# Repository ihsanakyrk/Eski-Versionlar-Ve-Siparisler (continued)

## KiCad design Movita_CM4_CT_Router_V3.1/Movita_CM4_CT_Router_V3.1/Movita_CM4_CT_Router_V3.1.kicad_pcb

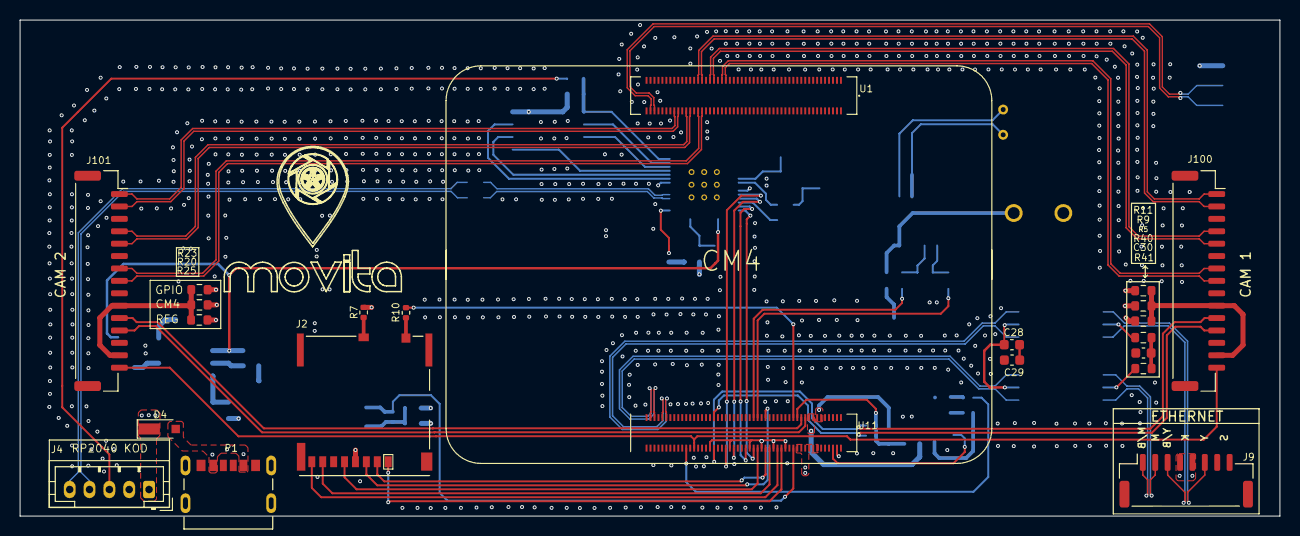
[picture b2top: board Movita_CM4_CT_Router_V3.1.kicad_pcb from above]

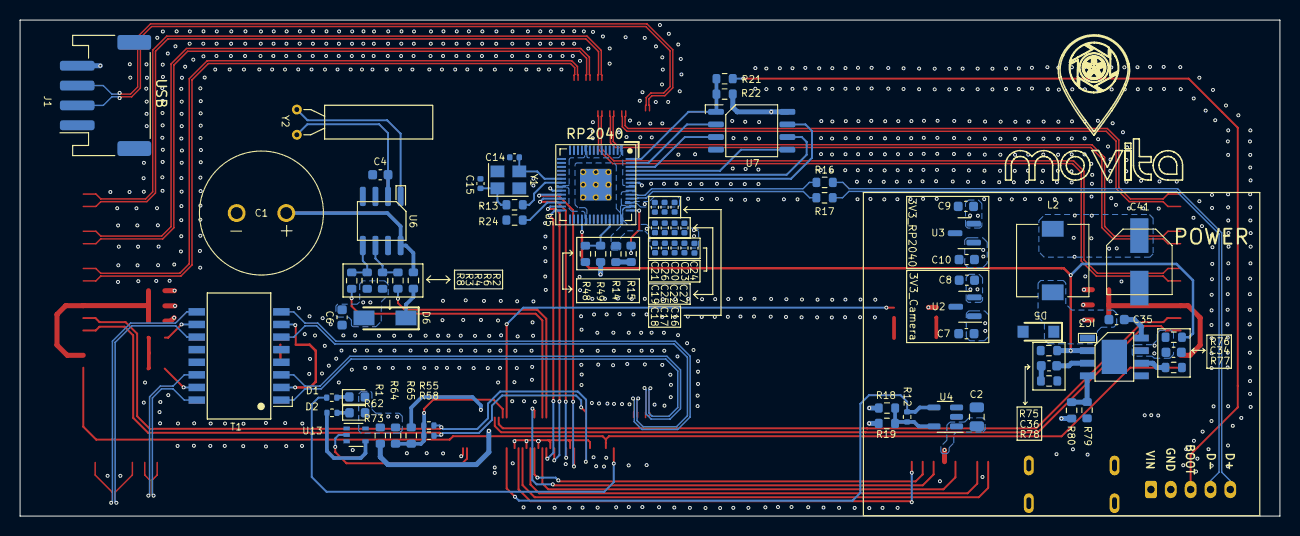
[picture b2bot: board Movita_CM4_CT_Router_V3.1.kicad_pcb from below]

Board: 6 copper layers, 127.0 x 50.0 mm, 96 parts (74 on the bottom side), 100 nets.

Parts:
C1: SE-5R5 D224VYV (C-Type); SuperCapacitor
C2: 10u; C_0805_2012Metric
C4: 22pF; C_0603_1608Metric
C6, C35: 100nF; C_0603_1608Metric
C7, C8, C9, C10, C34: 10uF; C_0603_1608Metric
C14, C15: 27pF; C_0402_1005Metric
C16, C17, C20, C21, C22, C23, C24, C25, C26, C27: 100nF; C_0402_1005Metric
C18, C19: 1uF; C_0402_1005Metric
C28, C29: 0.01uF; C_0603_1608Metric
C30: 1000pF; C_0603_1608Metric
C36: 150pF; C_0603_1608Metric
C41: 100uF; CAPAE660X550N
D1: LED Green; LED_0603_1608Metric
D2: LED Red; LED_0603_1608Metric
D4: 2SS100L-W; 2SS100LW
D5: SS34FA
D6: SS14
IC3: MP1584EN; MP1584N
J1: JST_PH_S4B-PH-SM4-TB_1x04-1MP_P2.00mm_Horizontal_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; JST_PH_S4B-PH-SM4-TB_1x04-1MP_P2.00mm_Horizontal
J2: Micro_SD_Card_Det; SDCARD_MOLEX_503398-1892
J4: JST_PH_B5B-PH-K_1x05_P2.00mm_Vertical
J9: JST_1x8-1MP_P1.25mm_Vertical; JST_1x8_1MP_P1.25mm_Vertical
J100, J101: JST_1x15-1MP_P1.25mm_Vertical; JST_1x15-1MP_P1.25mm_Horizontal
L2: CDRH74NP-100MC-B; CDRH74NP100MCB
P1: TYPE-C 6P(073)
R1, R6, R8, R11, R18, R20, R24, R64: 0R; R_0603_1608Metric
R2: 150R; R_0603_1608Metric
R3, R4: 4.7K; R_0603_1608Metric
R5, R9, R19, R22, R23, R25, R65: DNP; R_0603_1608Metric
R7, R10: DNP; R_0402_1005Metric
R12: 12K 1%; R_0402_1005Metric
R13, R21, R48: 1K; R_0603_1608Metric
R14: 200R; R_0603_1608Metric
R15: 1R; R_0603_1608Metric
R16, R17: 27R; R_0603_1608Metric
R40, R41: 75R; R_0603_1608Metric
R49: 10K; R_0603_1608Metric
R55, R58: 2.2K 1%; R_0402_1005Metric
R62, R73: 1K; R_0402_1005Metric
R75: 2.2K; R_0603_1608Metric
R76, R78: 100K; R_0603_1608Metric
R77: 200K; R_0603_1608Metric
R79: 40.2K; R_0603_1608Metric
R80: 210K; R_0603_1608Metric
T1: H1102NL
U1: DF40C-100DS-0.4V; DF40C-100DS-0.4V_CM4_Unit_B
U2, U3: TLV76033DBZT; SOT-23
U4: RT9742GGJ5; SOT-23-5
U5: RP2040; RP2040-QFN-56
U6: PCF8563T; SOIC-8_3.9x4.9mm_P1.27mm
U7: W25Q128JVS; SOIC-8_5.23x5.23mm_P1.27mm
U11: DF40C-100DS-0.4V; DF40C-100DS-0.4V_CM4_Unit_A
U13: 74LVC1G07SE-7; SOT-353_SC-70-5
Y1: CRYSTAL 12MHz; Crystal_SMD_3225-4Pin_3.2x2.5mm
Y2: CRYSTAL 32.7680KHZ 12.5PF TH; Crystal_AT310_D3.0mm_L10.0mm_Horizontal

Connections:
+1V1: C16.1, C17.1, C18.1, U5.23 (DVDD), U5.45 (VREG_VOUT), U5.50 (DVDD)
/CM4/3.3V_Sensor: C6.1, C7.2, D6.2, R3.1, R4.1, R5.1, R19.1, R25.1, U2.1 (OUT)
/CM4/+1.8v: R65.1, U11.88 (+1.8v_(Output)), U11.90 (+1.8v_(Output))
/CM4/+5V: C41.1, J1.4, L2.2, R80.2, U11.77 (+5v_(Input)), U11.79 (+5v_(Input)), U11.81 (+5v_(Input)), U11.83 (+5v_(Input)), U11.85 (+5v_(Input)), U11.87 (+5v_(Input))
/CM4/CAM0_C_N: J100.7, U1.140 (CAM0_C_N)
/CM4/CAM0_C_P: J100.8, U1.142 (CAM0_C_P)
/CM4/CAM0_D0_N: J100.1, U1.128 (CAM0_D0_N)
/CM4/CAM0_D0_P: J100.2, U1.130 (CAM0_D0_P)
/CM4/CAM0_D1_N: J100.4, U1.134 (CAM0_D1_N)
/CM4/CAM0_D1_P: J100.5, U1.136 (CAM0_D1_P)
/CM4/CAM1_C_N: J101.7, U1.127 (CAM1_C_N)
/CM4/CAM1_C_P: J101.8, U1.129 (CAM1_C_P)
/CM4/CAM1_D0_N: J101.1, U1.115 (CAM1_D0_N)
/CM4/CAM1_D0_P: J101.2, U1.117 (CAM1_D0_P)
/CM4/CAM1_D1_N: J101.4, U1.121 (CAM1_D1_N)
/CM4/CAM1_D1_P: J101.5, U1.123 (CAM1_D1_P)
/CM4/CAM_GPIO: R9.1, R23.1, U11.97 (Camera_GPIO)
/CM4/CM4_+3.3v: D1.2 (A), D2.2 (A), R1.1, R7.1, R11.1, R18.1, R20.1, R64.1, U13.5 (VCC)
/CM4/CM4_PCF_SCL: R4.2, R6.1, U6.6 (SCL)
/CM4/CM4_PCF_SDA: R3.2, R8.1, U6.5 (SDA)
/CM4/GPIO2: R8.2, U11.58 (GPIO2)
/CM4/GPIO3: R6.2, U11.56 (GPIO3)
/CM4/GPIO14: U5.28 (GPIO17), U11.55 (GPIO14)
/CM4/GPIO15: U5.27 (GPIO16), U11.51 (GPIO15)
/CM4/GPIO21: J100.15, J101.15, U11.25 (GPIO21)
/CM4/GPIO24: U5.25 (SWD), U11.45 (GPIO24)
/CM4/GPIO25: U5.24 (SWCLK), U11.41 (GPIO25)
/CM4/GPIO_VREF: R55.1, R58.1, R64.2, R65.2, U11.78 (GPIO_VREF(1.8v/3.3v_Input))
/CM4/ID_SC: J100.11, R55.2, U11.35 (ID_SC)
/CM4/ID_SD: J100.12, R58.2, U11.36 (ID_SD)
/CM4/Reserved: R10.1, U11.76 (Reserved)
/CM4/SCL0: J101.11, U11.80 (SCL0)
/CM4/SDA0: J101.12, U11.82 (SDA0)
/CM4/SD_CLK: J2.5 (CLK), U11.57 (SD_CLK)
/CM4/SD_CMD: J2.3 (CMD), U11.62 (SD_CMD)
/CM4/SD_DAT0: J2.7 (DAT0), U11.63 (SD_DAT0)
/CM4/SD_DAT1: J2.8 (DAT1), U11.67 (SD_DAT1)
/CM4/SD_DAT2: J2.1 (DAT2), U11.69 (SD_DAT2)
/CM4/SD_DAT3: J2.2 (DAT3/CD), U11.61 (SD_DAT3)
/CM4/SD_PWR: C2.1, J2.4 (VDD), U4.1 (OUT)
/CM4/SD_PWR_ON: R12.2, U4.4 (EN), U11.75 (SD_PWR_ON)
/CM4/USB2_N: J1.3, U1.103 (USB2_N)
/CM4/USB2_P: J1.2, U1.105 (USB2_P)
/CM4/nPWR_LED: U11.95 (nPI_LED_PWR), U13.2
/Power Unit/+3V3: C10.2, C19.1, C20.1, C21.1, C22.1, C23.1, C24.1, C25.1, C26.1, C27.1, R14.1, R22.1, U3.1 (OUT), U5.1 (IOVDD), U5.10 (IOVDD), U5.22 (IOVDD), U5.33 (IOVDD), U5.42 (IOVDD), U5.44 (VREG_IN), U5.48 (USB_VDD), U5.49 (IOVDD), U7.8 (VCC)
/Power Unit/VIN: C8.2, C9.2, C34.2, D4.1, IC3.7 (VIN), J4.1, R49.1, R76.1, U2.2 (IN), U3.2 (IN)
/RP2040/GPIO21: IC3.2 (EN), R75.1, R76.2, U5.32 (GPIO21)
/RP2040/GPIO27_ADC1: R48.1, R49.2, U5.39 (GPIO27_ADC1)
/RP2040/QSPI_SCLK: U5.52 (QSPI_SCLK), U7.6 (CLK)
/RP2040/QSPI_SD0: U5.53 (QSPI_SD0), U7.5 (DI(IO0))
/RP2040/QSPI_SD1: U5.55 (QSPI_SD1), U7.2 (DO(IO1))
/RP2040/QSPI_SD2: U5.54 (QSPI_SD2), U7.3 (IO2)
/RP2040/QSPI_SD3: U5.51 (QSPI_SD3), U7.7 (IO3)
/RP2040/QSPI_SS: R21.1, R22.2, U5.56 (QSPI_SS), U7.1 (~CS)
/RP2040/USB_D+: R16.2, U5.47 (USB_DP)
/RP2040/USB_D-: R17.2, U5.46 (USB_DM)
/RP2040/USB_RP2040_D+: J4.5, R16.1
/RP2040/USB_RP2040_D-: J4.4, R17.1
/RP2040/XIN: C14.1, U5.20 (XIN), Y1.3
/RP2040/XOUT: R13.1, U5.21 (XOUT)
/RP2040/~USB_BOOT: J4.3, R21.2
ADC_VREF: R14.2, R15.1
GND: C1.2, C2.2, C4.2, C6.2, C7.1, C8.1, C9.1, C10.1, C14.2, C15.2, C16.2, C17.2, C18.2, C19.2, C20.2, C21.2, C22.2, C23.2, C24.2, C25.2, C26.2, C27.2, C29.2, C30.2, C34.1, C41.2, D5.2, IC3.5 (GND), IC3.9 (EP), J1.1, J2.6 (VSS), J2.11 (SHIELD), J4.2, J9.7, J9.8, J9.MP, J100.3, J100.6, J100.9, J100.13, J101.3, J101.6, J101.9, J101.13, P1.A12 (GND), P1.B12 (GND), P1.MP (SHIELD), R48.2, R75.2, R77.2, R78.2, R79.2, U1.107 (GND), U1.108 (GND), U1.113 (GND), U1.114 (GND), U1.119 (GND), U1.120 (GND), U1.125 (GND), U1.126 (GND), U1.131 (GND), U1.132 (GND), U1.137 (GND), U1.138 (GND), U1.144 (GND), U1.150 (GND), U1.155 (GND), U1.156 (GND), U1.161 (GND), U1.162 (GND), U1.167 (GND), U1.168 (GND), U1.173 (GND), U1.174 (GND), U1.179 (GND), U1.180 (GND), U1.185 (GND), U1.186 (GND), U1.191 (GND), U1.192 (GND), U1.197 (GND), U1.198 (GND), U2.3 (GND), U3.3 (GND), U4.2 (GND), U5.19 (TESTEN), U5.57 (GND), U6.4 (VSS), U7.4 (GND), U11.1 (GND), U11.2 (GND), U11.7 (GND), U11.8 (GND), U11.13 (GND), U11.14 (GND), U11.22 (GND), U11.23 (GND), U11.32 (GND), U11.33 (GND), U11.42 (GND), U11.43 (GND), U11.52 (GND), U11.53 (GND), U11.59 (GND), U11.60 (GND), U11.65 (GND), U11.66 (GND), U11.71 (GND), U11.74 (GND), U11.98 (GND), U13.3 (GND), Y1.2, Y1.4
unnamed: C15.1, R13.2, Y1.1
unnamed: C28.2, C29.1
unnamed: C30.1, R40.1, R41.1
unnamed: C36.1, R78.1
unnamed: D1.1 (K), R62.1
unnamed: D2.1 (K), R73.1
unnamed: D6.1, R2.1
unnamed: C35.2, IC3.8 (BST)
unnamed: C36.2, IC3.3 (COMP)
unnamed: IC3.4 (FB), R79.1, R80.1
unnamed: IC3.6 (FREQ), R77.1
unnamed: C35.1, D5.1, IC3.1 (SW), L2.1
unnamed: J2.10 (DET_A), R7.2
unnamed: J2.9 (DET_B), R10.2
unnamed: J100.10, J100.14, R5.2, R9.2, R11.2
unnamed: J101.10, J101.14, R20.2, R23.2, R25.2
unnamed: R1.2, U11.84 (+3.3v_(Output)), U11.86 (+3.3v_(Output))
unnamed: R73.2, U13.4
unnamed: C28.1, T1.2 (CT1), T1.7 (CT2)
unnamed: R40.2, T1.10 (CT3)
unnamed: R41.2, T1.15 (CT4)
unnamed: R12.1, R18.2, R19.2, U4.5 (IN)
unnamed: R15.2, U5.43 (ADC_AVDD)
unnamed: R24.1, U5.26 (RUN)
unnamed: U6.1 (OSCI), Y2.2
unnamed: C4.1, U6.2 (OSCO), Y2.1
unnamed: C1.1, R2.2, U6.8 (VDD)
unnamed: R62.2, U11.21 (PI_nLED_Activity)
RX_N: T1.8 (RD-), U11.12 (Ethernet_Pair0_P)
RX_P: T1.6 (RD+), U11.10 (Ethernet_Pair0_N)
TRD0_N: J9.2, T1.14 (TX-)
TRD0_P: J9.1, T1.16 (TX+)
TRD1_N: J9.6, T1.9 (RX-)
TRD1_P: J9.3, T1.11 (RX+)
TX_N: T1.3 (TD-), U11.6 (Ethernet_Pair1_N)
TX_P: T1.1 (TD+), U11.4 (Ethernet_Pair1_P)
VRAW: D4.2, J9.4, J9.5, P1.A9 (VBUS), P1.B9 (VBUS)

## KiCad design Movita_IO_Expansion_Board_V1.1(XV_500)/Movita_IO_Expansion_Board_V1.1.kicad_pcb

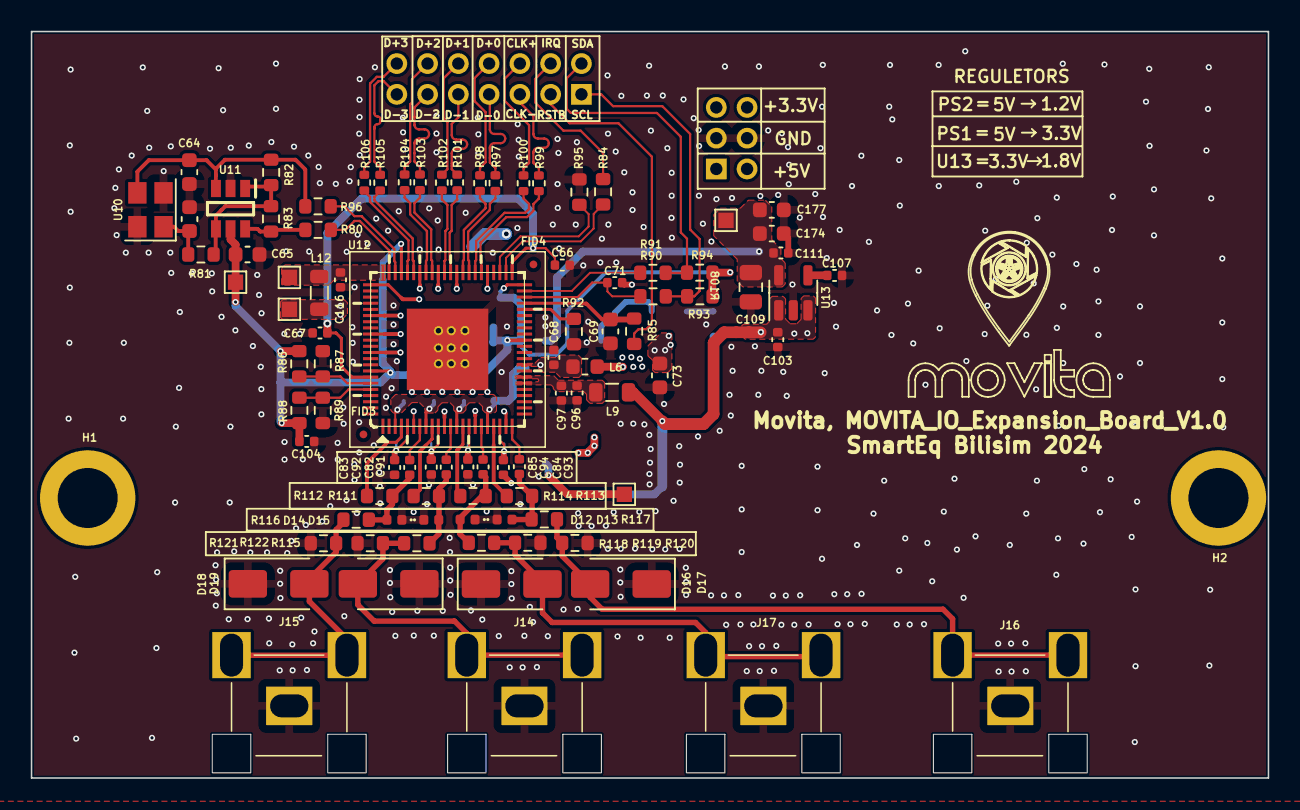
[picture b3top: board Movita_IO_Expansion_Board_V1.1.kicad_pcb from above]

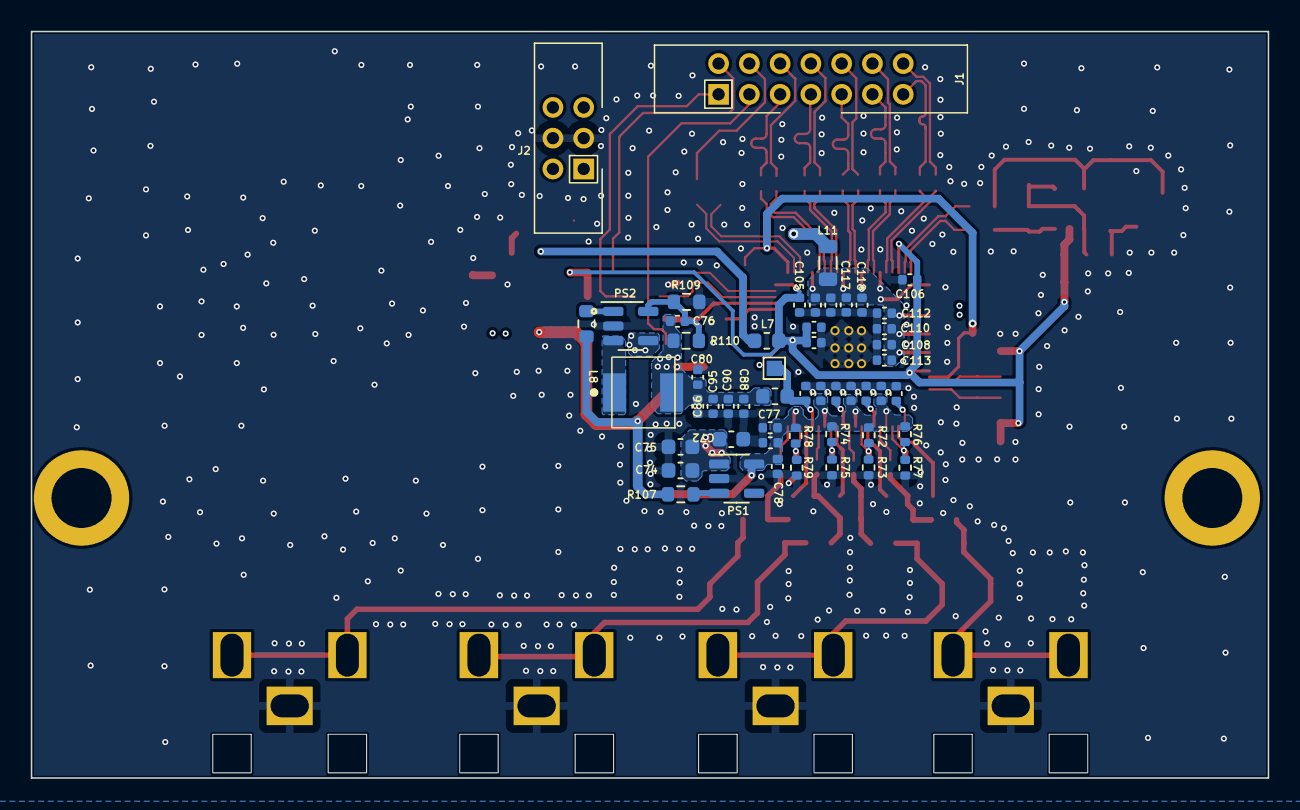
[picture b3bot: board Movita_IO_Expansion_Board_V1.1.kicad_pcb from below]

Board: 4 copper layers, 80.4 x 48.5 mm, 146 parts (52 on the bottom side), 75 nets.

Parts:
C63, C64: 8pF; C_0603_1608Metric
C65: 1uF; C_0603_1608Metric
C66, C67, C68, C70, C79, C81, C82, C83, C84, C85, C87, C89, C90, C91, C92, C93, C94, C95, C96, C98, C99, C100, C101, C102, C103, C104, C105, C106, C107, C108, C110, C111, C112, C113, C114, C115, C116, C117, C118: 100nF; C_0402_1005Metric
C69: 1nF; C_0603_1608Metric
C71: 56pF; C_0402_1005Metric
C72, C73: 10uF; C_0603_1608Metric
C74, C75, C177: 100nF; C_0603_1608Metric
C76: 100pF; C_0402_1005Metric
C77, C80, C86: 10uF; C_0402_1005Metric
C78, C88, C97: 4.7uF; C_0402_1005Metric
C109: 10uF; C_0805_2012Metric
C174: 4.7uF; C_0603_1608Metric
D12, D13, D14, D15: EZJZ800AA; D_0402_1005Metric
D16, D17, D18, D19: SMAJ30CA; D_SMA
FID3, FID4: DNP; Fiducial_0.5mm_Mask1mm
H1, H2: DNP; Screw_Terminal_1x1
J1: Conn_01x14_Pin; Analog signal connector
J2: Conn_01x06_Pin; Analog power connector
J14, J15, J16, J17: DNP; AV_CON
L6, L7: 742792651; L_0603_1608Metric
L8: YSPI0420-1R0M; HCM0420-1R0M
L9, L11, L12: YI201209U101-3R0T; L_0805_2012Metric
L10: CBW160808U101T; L_0603_1608Metric
PS1: RT9013-33GB; SOT-23-5
PS2: ETA3448S2F; SOT-23-5
R72, R74, R76, R78: 1M; R_0402_1005Metric
R73, R75, R77, R79: 510K; R_0402_1005Metric
R80, R81, R90, R91: 100R; R_0603_1608Metric
R82: 560K; R_0603_1608Metric
R83, R87, R89, R96: DNP; R_0603_1608Metric
R84, R85, R95: 0R; R_0603_1608Metric
R86, R88: 4.7K; R_0603_1608Metric
R92, R115, R116, R117, R118: 22R; R_0603_1608Metric
R93, R94: 2K; R_0603_1608Metric
R97, R98, R99, R100, R101, R102, R103, R104, R105, R106: 22R; R_0402_1005Metric
R107, R108: 10K; R_0603_1608Metric
R109, R110: 150K; R_0603_1608Metric
R111, R112, R113, R114: 47R; R_0603_1608Metric
R119, R120, R121, R122: 75R; R_0603_1608Metric
TP13, TP14, TP15, TP16, TP17, TP22: DNP; TestPoint_Pad_1.0x1.0mm
U10: CF4027M00010; Crystal_SMD_3225-4Pin_3.2x2.5mm
U11: NL27WZU04DTT1G
U12: TP2815; EPQFN_88L_10X10
U13: TP5108E23E-18; SOT-23-5

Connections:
/CSI_AHD/+3.3V: C103.1, J2.5, J2.6, L9.1, R107.1, R108.1, U13.1 (IN), U13.3 (EN)
/CSI_AHD/+5V: C72.1, C73.1, C74.1, C75.1, J2.1, J2.2, PS1.1 (VIN), PS2.4 (IN)
/CSI_AHD/CK1_N: R99.2, U12.50 (CKN_1)
/CSI_AHD/CK1_P: R100.2, U12.51 (CKP_1)
/CSI_AHD/D01_N: R97.2, U12.52 (D0N_1)
/CSI_AHD/D01_P: R98.2, U12.53 (D0P_1)
/CSI_AHD/D11_N: R101.2, U12.55 (D1N_1)
/CSI_AHD/D11_P: R102.2, U12.56 (D1P_1)
/CSI_AHD/D21_N: R103.2, U12.58 (D2N_1)
/CSI_AHD/D21_P: R104.2, U12.59 (D2P_1)
/CSI_AHD/D31_N: R105.2, U12.61 (D3N_1)
/CSI_AHD/D31_P: R106.2, U12.62 (D3P_1)
/CSI_AHD/DVDD: C66.2, C67.2, C68.2, L6.2, U12.31 (DVDD1), U12.45 (DVDD3), U12.82 (DVDD2)
/CSI_AHD/LX: L8.1, PS2.3 (LX)
/CSI_AHD/TP2855_CLK+: J1.6, R100.1
/CSI_AHD/TP2855_CLK-: J1.5, R99.1
/CSI_AHD/TP2855_D+0: J1.8, R98.1
/CSI_AHD/TP2855_D+1: J1.10, R102.1
/CSI_AHD/TP2855_D+2: J1.12, R104.1
/CSI_AHD/TP2855_D+3: J1.14, R106.1
/CSI_AHD/TP2855_D-0: J1.7, R97.1
/CSI_AHD/TP2855_D-1: J1.9, R101.1
/CSI_AHD/TP2855_D-2: J1.11, R103.1
/CSI_AHD/TP2855_D-3: J1.13, R105.1
/CSI_AHD/TP2855_IIC_ADDR0: R86.1, R87.2, U12.83 (SAD0)
/CSI_AHD/TP2855_IIC_ADDR1: R88.1, R89.2, U12.84 (SAD1)
/CSI_AHD/TP2855_IRQ: J1.4, R84.1
/CSI_AHD/TP2855_OSC_CLK_IN: R80.1, U12.65 (XTI)
/CSI_AHD/TP2855_OSC_CLK_OUT: R96.2, U12.64 (XTO)
/CSI_AHD/TP2855_PTZ1: R112.2, U12.4 (PTZ1)
/CSI_AHD/TP2855_PTZ2: R111.2, U12.9 (PTZ2)
/CSI_AHD/TP2855_PTZ3: R114.2, U12.14 (PTZ3)
/CSI_AHD/TP2855_PTZ4: R113.2, U12.19 (PTZ4)
/CSI_AHD/TP2855_RSTB: J1.3, R85.1
/CSI_AHD/TP2855_SCL: J1.1, R90.1, R93.2
/CSI_AHD/TP2855_SDA: J1.2, R91.1, R94.2
/CSI_AHD/TP2855_TEST_MODE: R95.2, U12.47 (TEST)
/CSI_AHD/TP2855_VIN1N: C83.1, R76.1, R77.2, U12.5 (VIN1N)
/CSI_AHD/TP2855_VIN1P: C92.1, U12.7 (VIN1)
/CSI_AHD/TP2855_VIN2N: C82.1, R72.1, R73.2, U12.10 (VIN2N)
/CSI_AHD/TP2855_VIN2P: C91.1, U12.12 (VIN2)
/CSI_AHD/TP2855_VIN3N: C85.1, R74.1, R75.2, U12.15 (VIN3N)
/CSI_AHD/TP2855_VIN3P: C94.1, U12.17 (VIN3)
/CSI_AHD/TP2855_VIN4N: C84.1, R78.1, R79.2, U12.20 (VIN4N)
/CSI_AHD/TP2855_VIN4P: C93.1, U12.22 (VIN4)
/CSI_AHD/TP2855_XOUT: C64.2, R82.2, R96.1, U10.3 (XOUT), U11.3 (INA2)
Earth: C63.1, C64.1, C65.2, C66.1, C67.1, C68.1, C69.1, C70.2, C71.1, C72.2, C73.2, C74.2, C75.2, C77.2, C78.2, C79.2, C80.2, C81.2, C82.2, C83.2, C84.2, C85.2, C86.2, C87.2, C88.2, C89.2, C90.2, C95.2, C96.2, C97.2, C98.2, C99.2, C100.2, C101.2, C102.2, C103.2, C104.2, C105.2, C106.2, C107.2, C108.2, C109.2, C110.2, C111.2, C112.2, C113.2, C114.2, C115.2, C116.2, C117.2, C118.2, C174.2, C177.2, D12.1 (A1), D13.1 (A1), D14.1 (A1), D15.1 (A1), D16.1 (A1), D17.1 (A1), D18.1 (A1), D19.1 (A1), J2.3, J2.4, J14.3, J15.3, J16.3, J17.3, PS1.2 (GND), PS2.2 (GND), R73.1, R75.1, R77.1, R79.1, R87.1, R89.1, R92.1, R95.1, R109.1, R119.2, R120.2, R121.2, R122.2, U10.2 (GND2), U10.4 (GND1), U11.2 (GND), U12.89 (EPAD), U13.2 (GND)
unnamed: C94.2, D12.2 (A2), R114.1, R118.2
unnamed: C93.2, D13.2 (A2), R113.1, R117.2
unnamed: C92.2, D14.2 (A2), R112.1, R116.2
unnamed: C91.2, D15.2 (A2), R111.1, R115.2
unnamed: D16.2 (A2), J17.1, J17.2, R118.1, R119.1
unnamed: D17.2 (A2), J16.1, J16.2, R117.1, R120.1
unnamed: D18.2 (A2), J15.1, J15.2, R116.1, R121.1
unnamed: D19.2 (A2), J14.1, J14.2, R115.1, R122.1
unnamed: PS1.3 (EN), R107.2
unnamed: PS2.1 (EN), R108.2
unnamed: C76.2, PS2.5 (OUT), R109.2, R110.1
unnamed: C63.2, R81.1, U10.1 (XIN)
unnamed: R81.2, R82.1, R83.2, U11.1 (INA1), U11.4 (OUT*Y2)
unnamed: R80.2, R83.1, U11.6 (OUT*Y1)
unnamed: R92.2, U12.40 (ALINKI)
unnamed: R84.2, U12.46 (IRQ)
unnamed: C69.2, R85.2, U12.41 (RSTB)
unnamed: C71.2, R90.2, U12.42 (SCL)
unnamed: R91.2, U12.43 (SDA)
unnamed: C107.1, U13.4 (BP)
TP2855_AVDD1V2: C98.1, C99.1, C100.1, C101.1, L10.2, TP15.1, U12.3 (AVDD1_1), U12.8 (AVDD1_2), U12.13 (AVDD1_3), U12.18 (AVDD1_4)
TP2855_AVDD3V3: C77.1, C78.1, C79.1, C81.1, C87.1, C89.1, PS1.5 (VOUT), R72.2, R74.2, R76.2, R78.2, TP13.1, U12.6 (AVDD3_1), U12.11 (AVDD3_2), U12.16 (AVDD3_3), U12.21 (AVDD3_4)
TP2855_AVDDPLL_1V2: C116.1, L12.2, TP17.1, U12.66 (VDDPPL)
TP2855_CODEC_V3V3: C96.1, C97.1, L9.2, U12.28 (AADVDD), U12.29 (ADAVDD)
TP2855_DVDD1V2: C108.1, C110.1, C112.1, C113.1, C114.1, C115.1, C117.1, C118.1, L11.2, U12.49 (VDDM2_1), U12.54 (VDDM1_1), U12.57 (VDDM3_1), U12.60 (VDDM4_1), U12.67 (VDDM1_2), U12.72 (VDDM4_2), U12.75 (VDDM2_2), U12.78 (VDDM3_2)
TP2855_VCCIO: C65.1, C70.1, C102.1, C104.1, C105.1, C106.1, L7.2, R86.2, R88.2, R93.1, R94.1, TP16.1, U11.5 (VCC), U12.35 (VDD_IO3), U12.44 (VDD_IO1), U12.63 (VDD_IO2), U12.81 (VDD_IO4)
VDDIO_18: C109.1, C111.1, C174.1, C177.1, L7.1, TP22.1, U13.5 (OUT)
VDD_1V2: C76.1, C80.1, C86.1, C88.1, C90.1, C95.1, L6.1, L8.2, L10.1, L11.1, L12.1, R110.2, TP14.1

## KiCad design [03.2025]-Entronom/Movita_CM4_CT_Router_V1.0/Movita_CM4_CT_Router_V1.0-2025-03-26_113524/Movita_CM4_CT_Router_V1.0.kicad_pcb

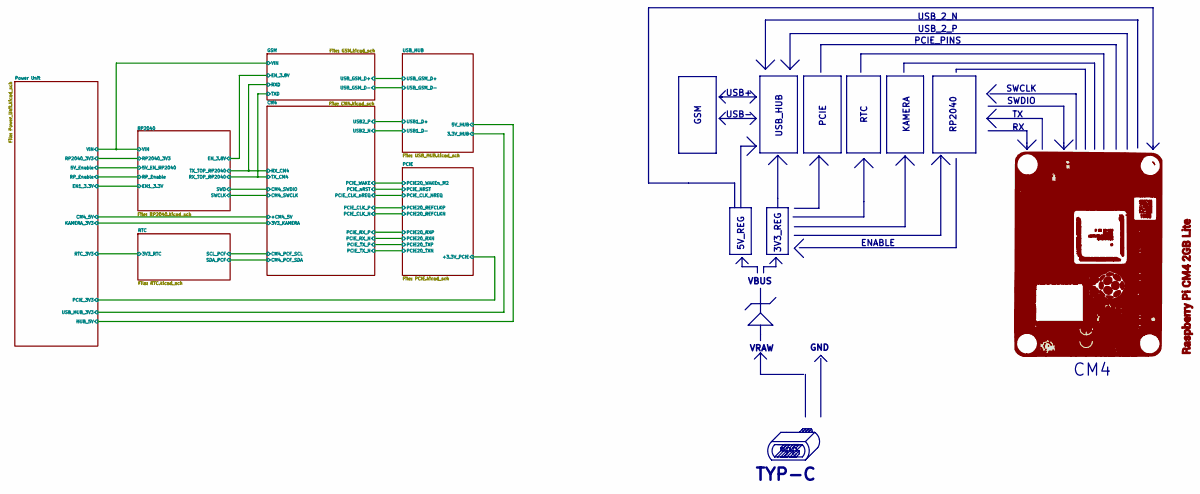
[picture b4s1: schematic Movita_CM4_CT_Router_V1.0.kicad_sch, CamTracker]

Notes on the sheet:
PCIE
PCIE_PINS
GND
5V_REG
SWDIO
KAMERA
CM4
GSM
RTC
USB-
SWCLK
VRAW
VBUS
USB_HUB
USB+
USB_2_N
USB_2_P
TYP-C
ENABLE
3V3_REG
RP2040

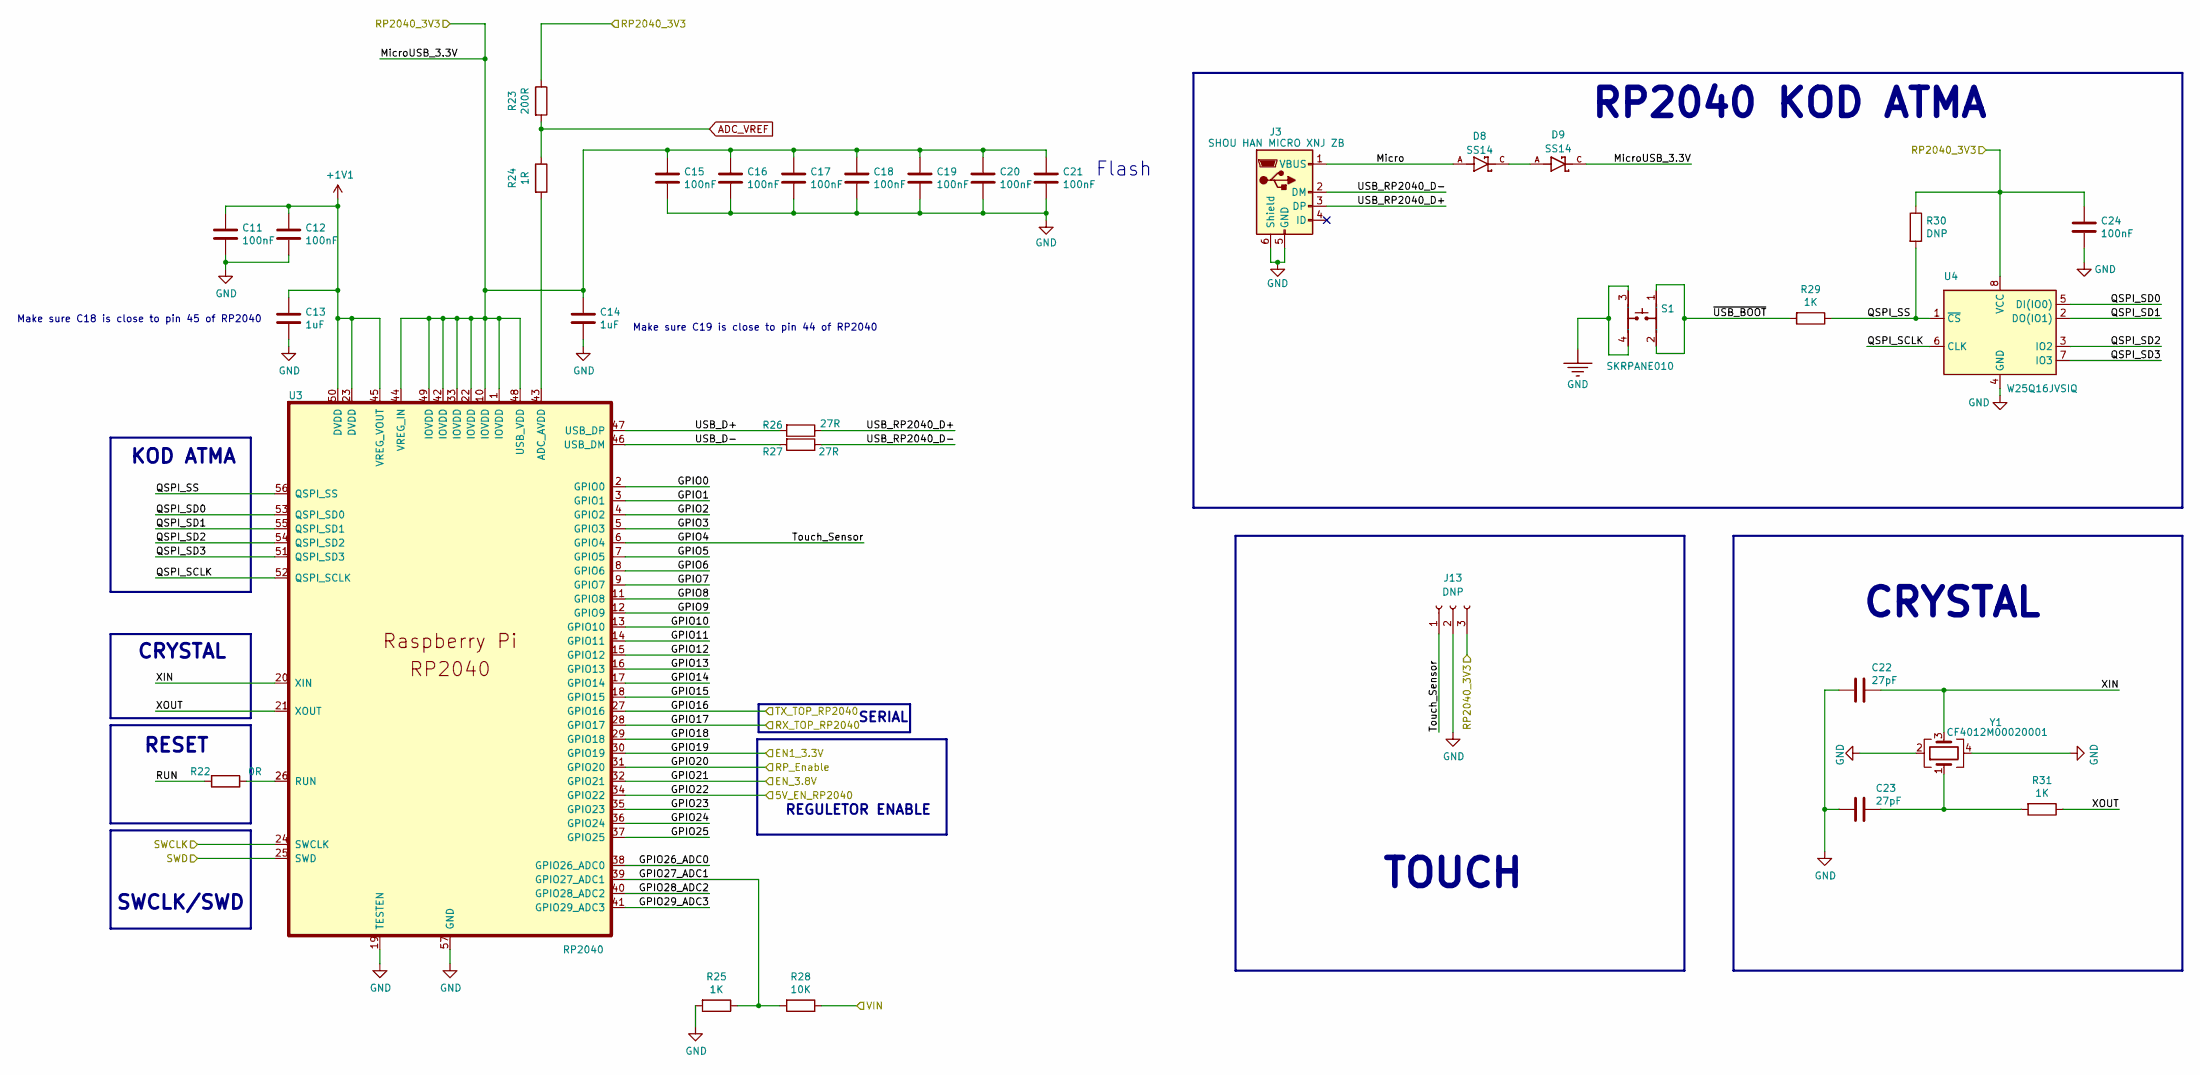
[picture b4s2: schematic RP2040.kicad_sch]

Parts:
C11, C12, C15, C16, C17, C18, C19, C20, C21, C24: 100nF; C_0402_1005Metric
C13, C14: 1uF; C_0402_1005Metric
C22, C23: 27pF; C_0603_1608Metric
D8, D9: SS14
J3: SHOU HAN MICRO XNJ ZB; Micro-B SMD; MPN SHOU HAN MICRO XNJ ZB
J13: DNP; PinSocket_1x03_P2.00mm_Vertical
R22: 0R; R_0402_1005Metric
R23: 200R; R_0402_1005Metric
R24: 1R; R_0402_1005Metric
R25: 1K; R_0402_1005Metric
R26, R27: 27R; R_0603_1608Metric
R28: 10K; R_0402_1005Metric
R29, R31: 1K; R_0603_1608Metric; MPN 0603WAF1001T5E
R30: DNP; R_0603_1608Metric
S1: SKRPANE010
U3: RP2040; RP2040-QFN-56; MPN RP2040
U4: W25Q16JVSIQ; SOIC-8_5.23x5.23mm_P1.27mm; MPN W25Q16JVSIQ
Y1: CF4012M00020001; Crystal_SMD_3225-4Pin_3.2x2.5mm; MPN CF4012M00020001

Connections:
+1V1: C11.1, C12.1, C13.1, U3.23 (DVDD), U3.45 (VREG_VOUT), U3.50 (DVDD)
/CM4/GPIO14: U3.28 (GPIO17); also elsewhere on the board
/CM4/GPIO15: U3.27 (GPIO16); also elsewhere on the board
/CM4/GPIO24: U3.25 (SWD); also elsewhere on the board
/CM4/GPIO25: U3.24 (SWCLK); also elsewhere on the board
/RP2040/GPIO0: U3.2 (GPIO0)
/RP2040/GPIO1: U3.3 (GPIO1)
/RP2040/GPIO2: U3.4 (GPIO2)
/RP2040/GPIO3: U3.5 (GPIO3)
/RP2040/GPIO4: J13.1, U3.6 (GPIO4)
/RP2040/GPIO5: U3.7 (GPIO5)
/RP2040/GPIO6: U3.8 (GPIO6)
/RP2040/GPIO7: U3.9 (GPIO7)
/RP2040/GPIO8: U3.11 (GPIO8)
/RP2040/GPIO9: U3.12 (GPIO9)
/RP2040/GPIO10: U3.13 (GPIO10)
/RP2040/GPIO11: U3.14 (GPIO11)
/RP2040/GPIO12: U3.15 (GPIO12)
/RP2040/GPIO13: U3.16 (GPIO13)
/RP2040/GPIO14: U3.17 (GPIO14)
/RP2040/GPIO15: U3.18 (GPIO15)
/RP2040/GPIO18: U3.29 (GPIO18)
/RP2040/GPIO19: U3.30 (GPIO19); also elsewhere on the board
/RP2040/GPIO20: U3.31 (GPIO20); also elsewhere on the board
/RP2040/GPIO21: U3.32 (GPIO21); also elsewhere on the board
/RP2040/GPIO22: U3.34 (GPIO22); also elsewhere on the board
/RP2040/GPIO23: U3.35 (GPIO23)
/RP2040/GPIO24: U3.36 (GPIO24)
/RP2040/GPIO25: U3.37 (GPIO25)
/RP2040/GPIO26_ADC0: U3.38 (GPIO26_ADC0)
/RP2040/GPIO27_ADC1: R25.1, R28.2, U3.39 (GPIO27_ADC1)
/RP2040/GPIO28_ADC2: U3.40 (GPIO28_ADC2)
/RP2040/GPIO29_ADC3: U3.41 (GPIO29_ADC3)
/RP2040/Micro: D8.A, J3.1 (VBUS)
/RP2040/MicroUSB_3.3V: C14.1, C15.1, C16.1, C17.1, C18.1, C19.1, C20.1, C21.1, C24.1, D9.C, J13.3, R23.1, R30.1, U3.1 (IOVDD), U3.10 (IOVDD), U3.22 (IOVDD), U3.33 (IOVDD), U3.42 (IOVDD), U3.44 (VREG_IN), U3.48 (USB_VDD), U3.49 (IOVDD), U4.8 (VCC); also elsewhere on the board
/RP2040/QSPI_SCLK: U3.52 (QSPI_SCLK), U4.6 (CLK)
/RP2040/QSPI_SD0: U3.53 (QSPI_SD0), U4.5 (DI(IO0))
/RP2040/QSPI_SD1: U3.55 (QSPI_SD1), U4.2 (DO(IO1))
/RP2040/QSPI_SD2: U3.54 (QSPI_SD2), U4.3 (IO2)
/RP2040/QSPI_SD3: U3.51 (QSPI_SD3), U4.7 (IO3)
/RP2040/QSPI_SS: R29.1, R30.2, U3.56 (QSPI_SS), U4.1 (~CS)
/RP2040/RUN: R22.2
/RP2040/USB_D+: R26.2, U3.47 (USB_DP)
/RP2040/USB_D-: R27.2, U3.46 (USB_DM)
/RP2040/USB_RP2040_D+: J3.3 (DP), R26.1
/RP2040/USB_RP2040_D-: J3.2 (DM), R27.1
/RP2040/XIN: C22.1, U3.20 (XIN), Y1.3
/RP2040/XOUT: R31.1, U3.21 (XOUT)
/RP2040/~USB_BOOT: R29.2, S1.1, S1.2
ADC_VREF: R23.2, R24.1
Earth: C11.2, C12.2, C13.2, C14.2, C15.2, C16.2, C17.2, C18.2, C19.2, C20.2, C21.2, C22.2, C23.2, C24.2, J3.5 (GND), J3.6 (Shield), J13.2, R25.2, S1.3, S1.4, U3.19 (TESTEN), U3.57 (GND), U4.4 (GND), Y1.2, Y1.4; also elsewhere on the board
unnamed: C23.1, R31.2, Y1.1
unnamed: D8.C, D9.A
unnamed: R24.2, U3.43 (ADC_AVDD)
unnamed: R22.1, U3.26 (RUN)
VIN: R28.1; also elsewhere on the board

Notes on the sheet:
RESET
Make sure C18 is close to pin 45 of RP2040
Make sure C19 is close to pin 44 of RP2040
REGULETOR ENABLE
SWCLK/SWD
Flash
KOD ATMA
CRYSTAL
RP2040 KOD ATMA
SERIAL
TOUCH

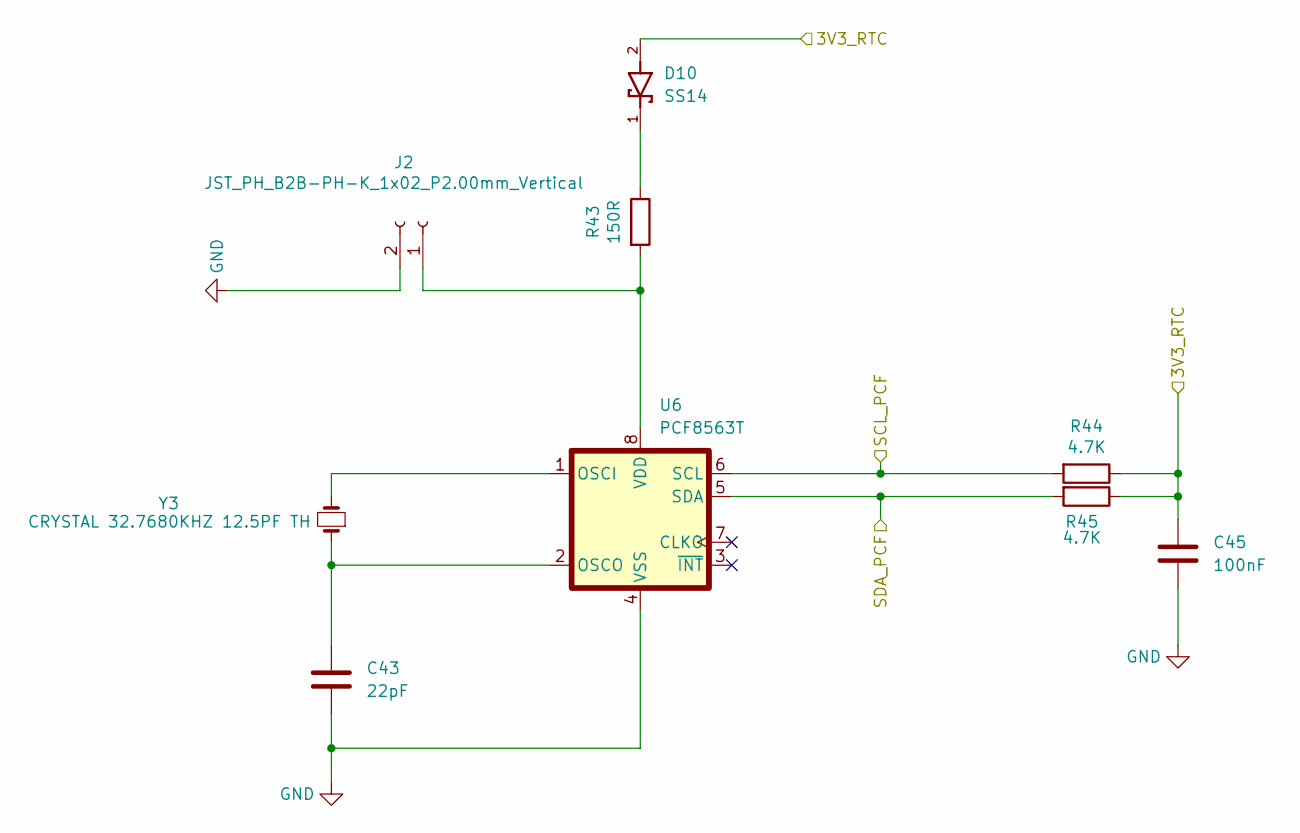
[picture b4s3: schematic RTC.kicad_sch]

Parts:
C43: 22pF; C_0603_1608Metric
C45: 100nF; C_0603_1608Metric
D10: SS14
J2: JST_PH_B2B-PH-K_1x02_P2.00mm_Vertical; MPN JST_PH_B2B-PH-K_1x02_P2.00mm_Vertical
R43: 150R; R_0603_1608Metric
R44, R45: 4.7K; R_0603_1608Metric
U6: PCF8563T; SOIC-8_3.9x4.9mm_P1.27mm; MPN PCF8563T/5,518
Y3: CRYSTAL 32.7680KHZ 12.5PF TH; Crystal_AT310_D3.0mm_L10.0mm_Horizontal; MPN CFS20632768DZFB

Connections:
/CM4/CM4_PCF_SCL: R44.2, U6.6 (SCL); also elsewhere on the board
/CM4/CM4_PCF_SDA: R45.2, U6.5 (SDA); also elsewhere on the board
/Power Unit/RTC_3V3: C45.1, D10.2, R44.1, R45.1; also elsewhere on the board
Earth: C43.2, C45.2, J2.2, U6.4 (VSS); also elsewhere on the board
unnamed: D10.1, R43.1
unnamed: J2.1, R43.2, U6.8 (VDD)
unnamed: U6.1 (OSCI), Y3.2
unnamed: C43.1, U6.2 (OSCO), Y3.1

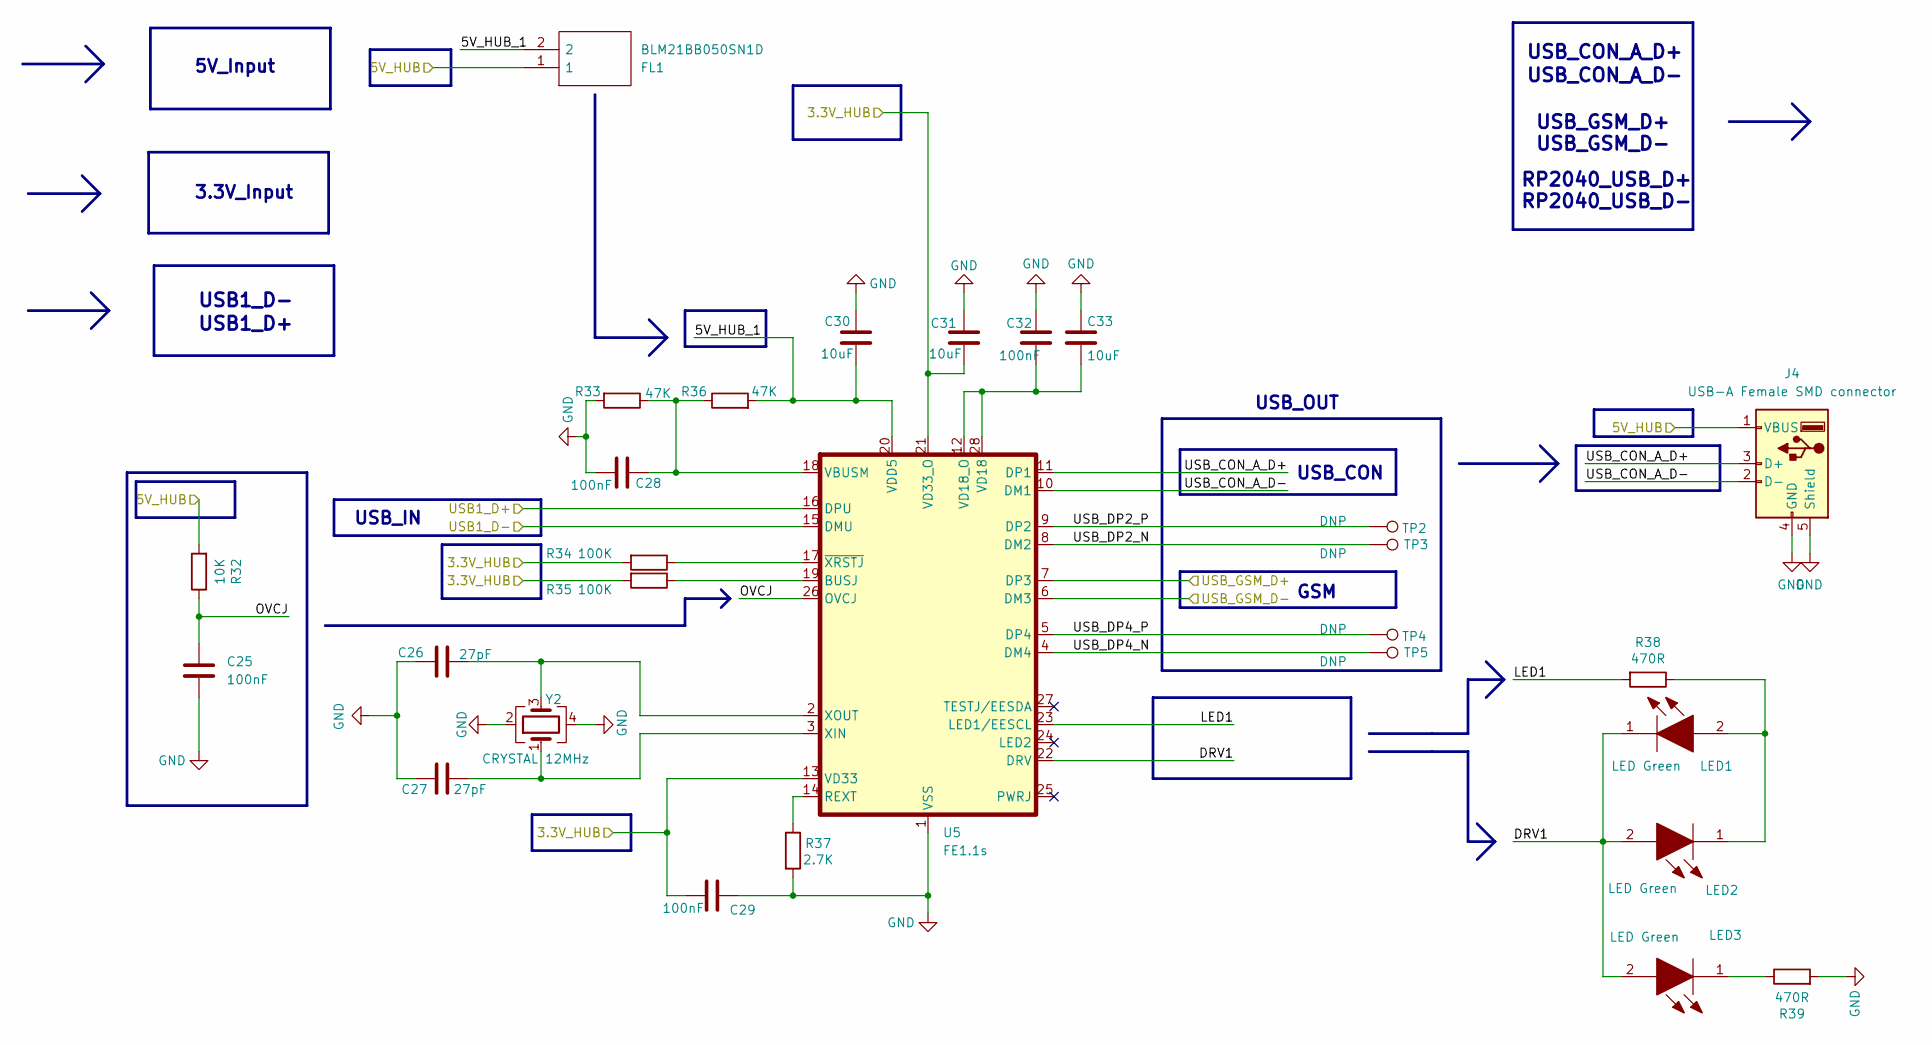
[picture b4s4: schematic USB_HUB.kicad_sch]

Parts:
C25, C29, C32: 100nF; C_0603_1608Metric
C26, C27: 27pF; C_0402_1005Metric
C28: 100nF; C_0402_1005Metric
C30, C31: 10uF; C_0402_1005Metric
C33: 10uF; C_0603_1608Metric
FL1: BLM21BB050SN1D; BLM21BB050SH1D; Manufacturer_Part_Number BLM21BB050SN1D; Mouser Part Number 81-BLM21B050S
J4: USB-A Female SMD connector; USB_A_Stewart_SS-52100-001_Horizontal
LED1, LED2, LED3: LED Green; LED_0805_2012Metric; Manufacturer_Part_Number 150080VS75000; Mouser Part Number 710-150080VS75000
R32: 10K; R_0603_1608Metric
R33, R36: 47K; R_0603_1608Metric
R34, R35: 100K; R_0603_1608Metric
R37: 2.7K; R_0603_1608Metric
R38, R39: 470R; R_0603_1608Metric
TP2, TP3, TP4, TP5: DNP; TestPoint_Pad_D1.0mm
U5: FE1.1s; SSOP-28_3.9x9.9mm_P0.635mm; MPN FE1.1S-BSOP28BCN
Y2: CRYSTAL 12MHz; Crystal_SMD_3225-4Pin_3.2x2.5mm; MPN CF4012M00020001

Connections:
/CM4/USB2_N: U5.15 (DMU); also elsewhere on the board
/CM4/USB2_P: U5.16 (DPU); also elsewhere on the board
/GSM/USB_GSM_D+: U5.7 (DP3); also elsewhere on the board
/GSM/USB_GSM_D-: U5.6 (DM3); also elsewhere on the board
/Power Unit/HUB_5V: FL1.1, J4.1 (VBUS), R32.2; also elsewhere on the board
/Power Unit/USB_HUB_3V3: C29.1, C31.2, R34.2, R35.2, U5.13 (VD33), U5.21 (VD33_O); also elsewhere on the board
/USB_HUB/5V_HUB_1: C30.2, FL1.2, R36.2, U5.20 (VDD5)
/USB_HUB/DRV1: LED1.1, LED2.2, LED3.2, U5.22 (DRV)
/USB_HUB/LED1: R38.2, U5.23 (LED1/EESCL)
/USB_HUB/OVCJ: C25.1, R32.1, U5.26 (OVCJ)
/USB_HUB/USB_CON_A_D+: J4.3 (D+), U5.11 (DP1)
/USB_HUB/USB_CON_A_D-: J4.2 (D-), U5.10 (DM1)
/USB_HUB/USB_DP2_N: TP3.1, U5.8 (DM2)
/USB_HUB/USB_DP2_P: TP2.1, U5.9 (DP2)
/USB_HUB/USB_DP4_N: TP5.1, U5.4 (DM4)
/USB_HUB/USB_DP4_P: TP4.1, U5.5 (DP4)
Earth: C25.2, C26.2, C27.2, C28.2, C29.2, C30.1, C31.1, C32.2, C33.2, J4.4 (GND), J4.5 (Shield), R33.2, R37.2, R39.2, U5.1 (VSS), Y2.2, Y2.4; also elsewhere on the board
unnamed: LED1.2, LED2.1, R38.1
unnamed: LED3.1, R39.1
unnamed: R35.1, U5.19 (BUSJ)
unnamed: R37.1, U5.14 (REXT)
unnamed: C28.1, R33.1, R36.1, U5.18 (VBUSM)
unnamed: C32.1, C33.1, U5.12 (VD18_O), U5.28 (VD18)
unnamed: C27.1, U5.3 (XIN), Y2.1
unnamed: C26.1, U5.2 (XOUT), Y2.3
unnamed: R34.1, U5.17 (~XRSTJ)

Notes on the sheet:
USB1_D+
USB_GSM_D+
GSM
USB_CON_A_D+
USB_IN
5V_Input
RP2040_USB_D+
USB_CON_A_D-
USB_GSM_D-
RP2040_USB_D-
USB_OUT
USB1_D-
3.3V_Input
USB_CON
